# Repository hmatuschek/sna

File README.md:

# Scalar Network Analyzer

A [scalar network analyzer](https://en.wikipedia.org/wiki/Network_analyzer_%28electrical%29) (SNA) measures the amplitude of an output signal of a circuit as a function of the input frequency.

This project provides the circuit, firmware and software to implement a very simple and cheap SNA. It uses a [AD9850 DDS module](http://www.minikits.com.au/electronic-kits/dds-synthesizer/basic-dds/AD9850-DDS-01) as the programmable signal generator and a AD8307 logarithmic amplifier in conjecture with the ADC of an ATMEGA 168 (or the pin compatible ATMEGA 8/48/88/328) to record the input amplitude. The SNA hardware is interfaced via the common RS-232 using a MAX232 level converter. The firmware for the ATMEGA 168 can be found in the firmware directory.

The client software then provides a simple means of performing the measurements and displays the results. It provides two operating modes. The <emph>poll</emph> mode outputs a fixed frequency and measures the input amplitude while the <emph>scan</emph> mode records the input amplitude as a function of the output frequency. The result is then plotted (see above). 

## Hardware
As mentioned above, the [circuit](https://github.com/hmatuschek/sna/raw/master/doc/compact_scm.pdf) consists of an AD9850 DDS module (visible below) an ATMEGA 168 (partially covered in the picture) to program the DDS and to measure the output voltage of the logarithmic amplifier (AD8307, visible in the top-left corner). The logarithmic amplifier converts the input power over a 51 Ohms resistor into a voltage (0-2.5V) which is a linear function of the input power in dBm. 

The AD8307 can handle up to 17dBm (50mW). The output power of the DDS, however, is only about 0.1mW (-10dBm). To enhence the dynamic range of the SNA, a buffer amplifier (two 2N3904, circuit stolen from  [here](http://rheslip.blogspot.de/2015/08/the-simple-scalar-network-analyser.html), visible at the bottom-right corner) is used to increase the output to about 1-3mW (0-5dBm).  

The SNA is interfaced through the UART (RS-232) of the ATMEGA using a MAX232 level converter (visible in the bottom-left corner). In fact, the hardware is ARDUINO UNO compatible. By flashing the ARDUINO bootloader onto the ATMEGA, the SNA can be programmed easily via the RS-232 interface. 

The [board](https://github.com/hmatuschek/sna/raw/master/doc/compact_brd.pdf) is routed such that it is possible to assemble the circuit on a perfboard without bridges. The board dimensions are kept small. The complete circuit fits into a relatively small TEKO 2/A chassis (57 x 72 x 28 mm). For a better performance, the distance between the AD8307 logarithmic amplifier and the rest of the circuit should be increased and the AD8307 should also be shielded. Due to the lack of shielding, my prototype has a relatively large noise level of about -40dBm.

## Firmware
The firmware for the ATMEGA 168 is extremely simply. It just waits for commands received via the serial interface and either sets the frequency of the DDS module, measures the input amplitude or shuts the DDS chip down. 

### Protocol
The communication protocol is a simple binary protocol. The host (computer) sends a command to the device (SNA) and receives a response. The device never sends data without a request. 

#### Read amplitude
This command will tell the SNA to read the current amplitude.

##### Request 
```
  +------+
  | 0x01 |
  +------+
```
##### Response 
On success 
```
  +------+------+------+
  | 0x00 |  16b value  |
  +------+------+------+
```
The 16bit value (big endian) represents the 16bit fraction of the output voltage of the AD8307. This value maps linear to the dBm value where 0 represents -84dBm and 65535 17dBm.

On error  
```
  +------+
  | 0x01 |
  +------+
```

#### Set frequency
Sets the frequency of the DDS chip.

##### Request 
```
  +------+------+------+------+------+
  | 0x02 |     32b frequency word    |
  +------+------+------+------+------+
```
The 32 bit frequency word (big endian) represents the fraction of the output frequency relative to the oscillator frequency (125MHz). I.e. F_out = 125MHz * FW/2^32

##### Response 
On success 
```
  +------+
  | 0x00 |
  +------+
```
On error  
```
  +------+
  | 0x01 |
  +------+
```

#### Set frequency & read amplitude
Sets the frequency of the DDS chip and reads the current amplitude value.

##### Request 
(see set frequency command above)
```
  +------+------+------+------+------+
  | 0x03 |     32b frequency word    |
  +------+------+------+------+------+
```

##### Response 
On success 
```
  +------+------+------+
  | 0x00 |  16b value  |
  +------+------+------+
```
(see read amplitude command above)

On error  
```
  +------+
  | 0x01 |
  +------+
```

#### Shutdown DDS

This command will disable the DDS output. 

##### Request 
```
  +------+
  | 0x04 |
  +------+
```

##### Response 
On success 
```
  +------+
  | 0x00 |
  +------+
```

On error  
```
  +------+
  | 0x01 |
  +------+
```

## License
SNA - A simple scalar network analyzer. (c) 2015 Hannes Matuschek <hmatuschek at gmail dot com>

The hardware is licensed under [Createtive Commons BY-SA 4.0](https://creativecommons.org/licenses/by-sa/4.0/) and the software under [GPL 2.0+](https://www.gnu.org/licenses/old-licenses/gpl-2.0.txt) (see below).

This program is free software; you can redistribute it and/or
modify it under the terms of the GNU General Public License
as published by the Free Software Foundation; either version 2
of the License, or (at your option) any later version.</p>

This program is distributed in the hope that it will be useful,
but WITHOUT ANY WARRANTY; without even the implied warranty of
MERCHANTABILITY or FITNESS FOR A PARTICULAR PURPOSE.  See the
GNU General Public License for more details.

You should have received a copy of the GNU General Public License
along with this program; if not, write to the Free Software
Foundation, Inc., 51 Franklin Street, Fifth Floor, Boston, MA  02110-1301, USA.

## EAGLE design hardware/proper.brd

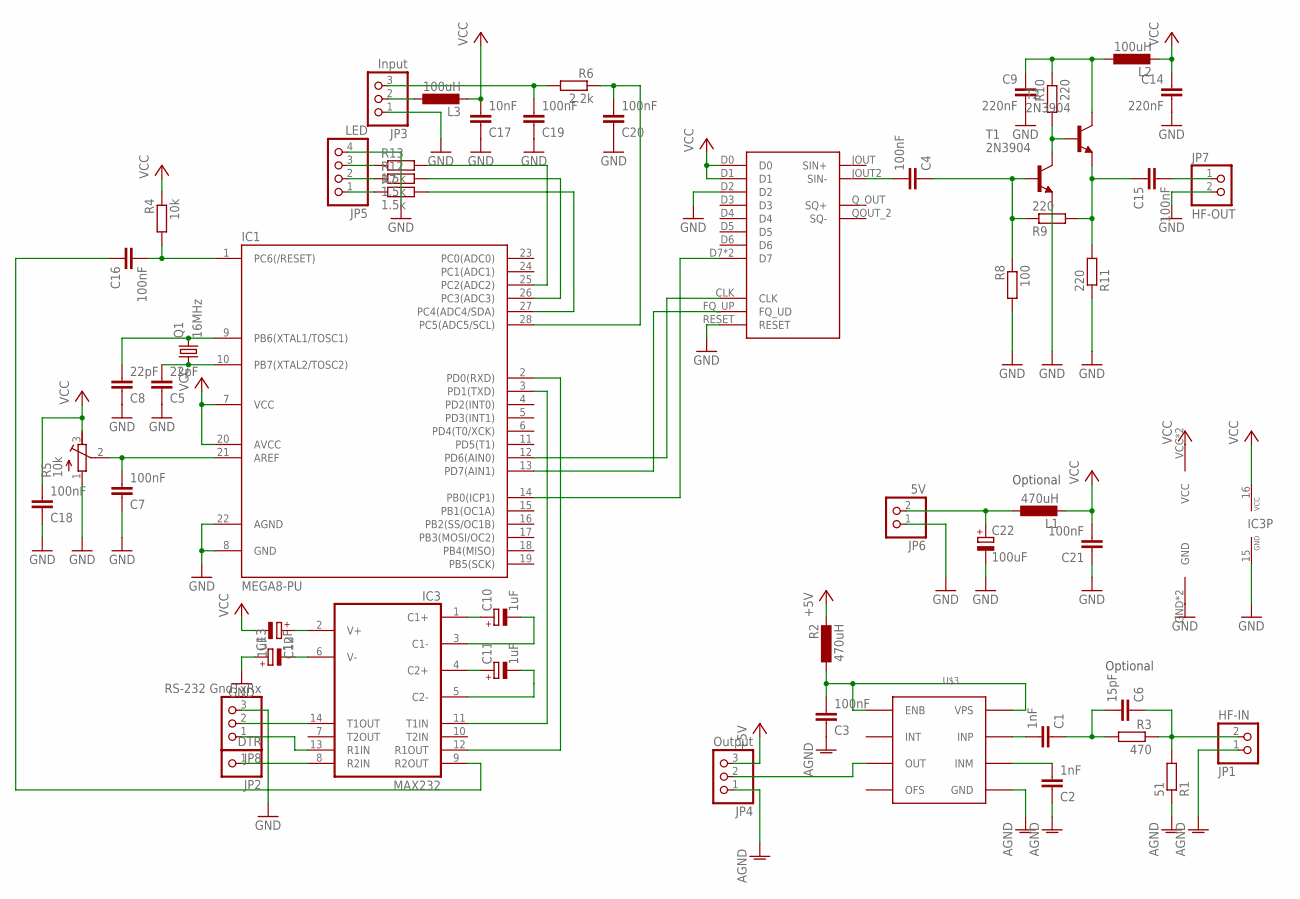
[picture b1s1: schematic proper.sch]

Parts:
C1, C2: 1nF; C025-025X050
C3, C4, C7, C19, C20, C21: 100nF; C025-025X050
C5: 22pF; C102-043X133
C6: 15pF; C050-025X075
C8: 22pF; C025-025X050
C9: 220nF; C025-025X050
C10, C11, C12, C13: 1uF; E2,5-5
C14: 220nF; C050-025X075
C15, C18: 100nF; C050-025X075
C16: 100nF; C075-032X103
C17: 10nF; C025-025X050
C22: 100uF; E2,5-6
IC1: MEGA8-PU; DIL28-3
IC3: MAX232; DIL16
JP1: HF-IN; 1X02
JP2: DTR; 1X01
JP3: Input; 1X03
JP4: Output; 1X03
JP5: LED; 1X04
JP6: 5V; 1X02
JP7: HF-OUT; 1X02
JP8: RS-232 GndTxRx; 1X03
L1: 470uH; 0207/5V
L2: 100uH; 0207/12
L3: 100uH; 0207/2V
Q1: 16MHz; HC49U-V
R1: 51; 0204V
R2: 470uH; 0204/5
R3: 470; 0204/5
R4: 10k; 0204/5
R5: 10k; RTRIM64W
R6: 2.2k; 0204V
R7, R12, R13: 1.5k; 0204/5
R8: 100; 0204V
R9, R10, R11: 220; 0204V
T1, T2: 2N3904; TO92-EBC
U$1: DDS-1
U$3: AD8307; DIL08

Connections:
+5V: JP4.3, R2.2
GND: C5.1, C7.1, C8.1, C9.2, C13.+, C14.2, C17.1, C18.1, C19.1, C20.1, C21.1, C22.-, IC1.8 (GND), IC1.22 (AGND), IC3.15 (GND), JP3.1, JP5.4, JP6.1, JP7.2, JP8.3, R5.1 (A), R8.2, R11.1, T1.E, U$1.D2, U$1.GND, U$1.GND2 (GND), U$1.RESET
unnamed: C4.2, U$1.JOUT2 (SIN-)
unnamed: C6.1, JP1.2, R1.2, R3.1
unnamed: C1.2, U$3.8 (INP)
unnamed: C2.2, U$3.1 (INM)
unnamed: C5.2, IC1.10 (PB7(XTAL2/TOSC2)), Q1.1
unnamed: C8.2, IC1.9 (PB6(XTAL1/TOSC1)), Q1.2
unnamed: C12.+, IC3.2 (V+)
unnamed: C3.2, R2.1, U$3.6 (ENB), U$3.7 (VPS)
unnamed: JP4.2, U$3.4 (OUT)
unnamed: C22.+, JP6.2, L1.1
unnamed: IC3.14 (T1OUT), JP8.2
unnamed: C1.1, C6.2, R3.2
unnamed: C4.1, R8.1, R9.1, T1.B
unnamed: C20.2, IC1.28 (PC5(ADC5/SCL)), R6.1
unnamed: IC1.13 (PD7(AIN1)), U$1.FQ_UP (FQ_UD)
unnamed: C13.-, IC3.6 (V-)
unnamed: IC1.3 (PD1(TXD)), IC3.11 (T1IN)
unnamed: IC1.12 (PD6(AIN0)), U$1.CLK
unnamed: IC1.14 (PB0(ICP1)), U$1.D7, U$1.D7_2 (D7)
unnamed: C9.1, L2.1, R10.1, T2.C
unnamed: R10.2, T1.C, T2.B
unnamed: IC1.2 (PD0(RXD)), IC3.12 (R1OUT)
unnamed: C15.2, JP7.1
unnamed: C15.1, R9.2, R11.2, T2.E
unnamed: C16.2, IC1.1 (PC6(/RESET)), R4.2
unnamed: C16.1, IC3.9 (R2OUT)
unnamed: IC3.8 (R2IN), JP2.1
unnamed: C7.2, IC1.21 (AREF), R5.2 (S)
unnamed: JP3.2, L3.1
unnamed: JP5.1, R7.1
unnamed: JP5.2, R12.1
unnamed: JP5.3, R13.1
unnamed: C2.1, C3.1, JP1.1, JP4.1, R1.1, U$3.2 (GND)
unnamed: IC3.13 (R1IN), JP8.1
unnamed: IC1.27 (PC4(ADC4/SDA)), R7.2
unnamed: IC1.26 (PC3(ADC3)), R12.2
unnamed: IC1.25 (PC2(ADC2)), R13.2
unnamed: C10.+, IC3.1 (C1+)
unnamed: C10.-, IC3.3 (C1-)
unnamed: C11.+, IC3.4 (C2+)
unnamed: C11.-, IC3.5 (C2-)
unnamed: C19.2, JP3.3, R6.2
VCC: C12.-, C14.1, C17.2, C18.2, C21.2, IC1.7 (VCC), IC1.20 (AVCC), IC3.16 (VCC), L1.2, L2.2, L3.2, R4.1, R5.3 (E), U$1.D0, U$1.D1, U$1.VCC, U$1.VCC2 (VCC)

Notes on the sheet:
Optional

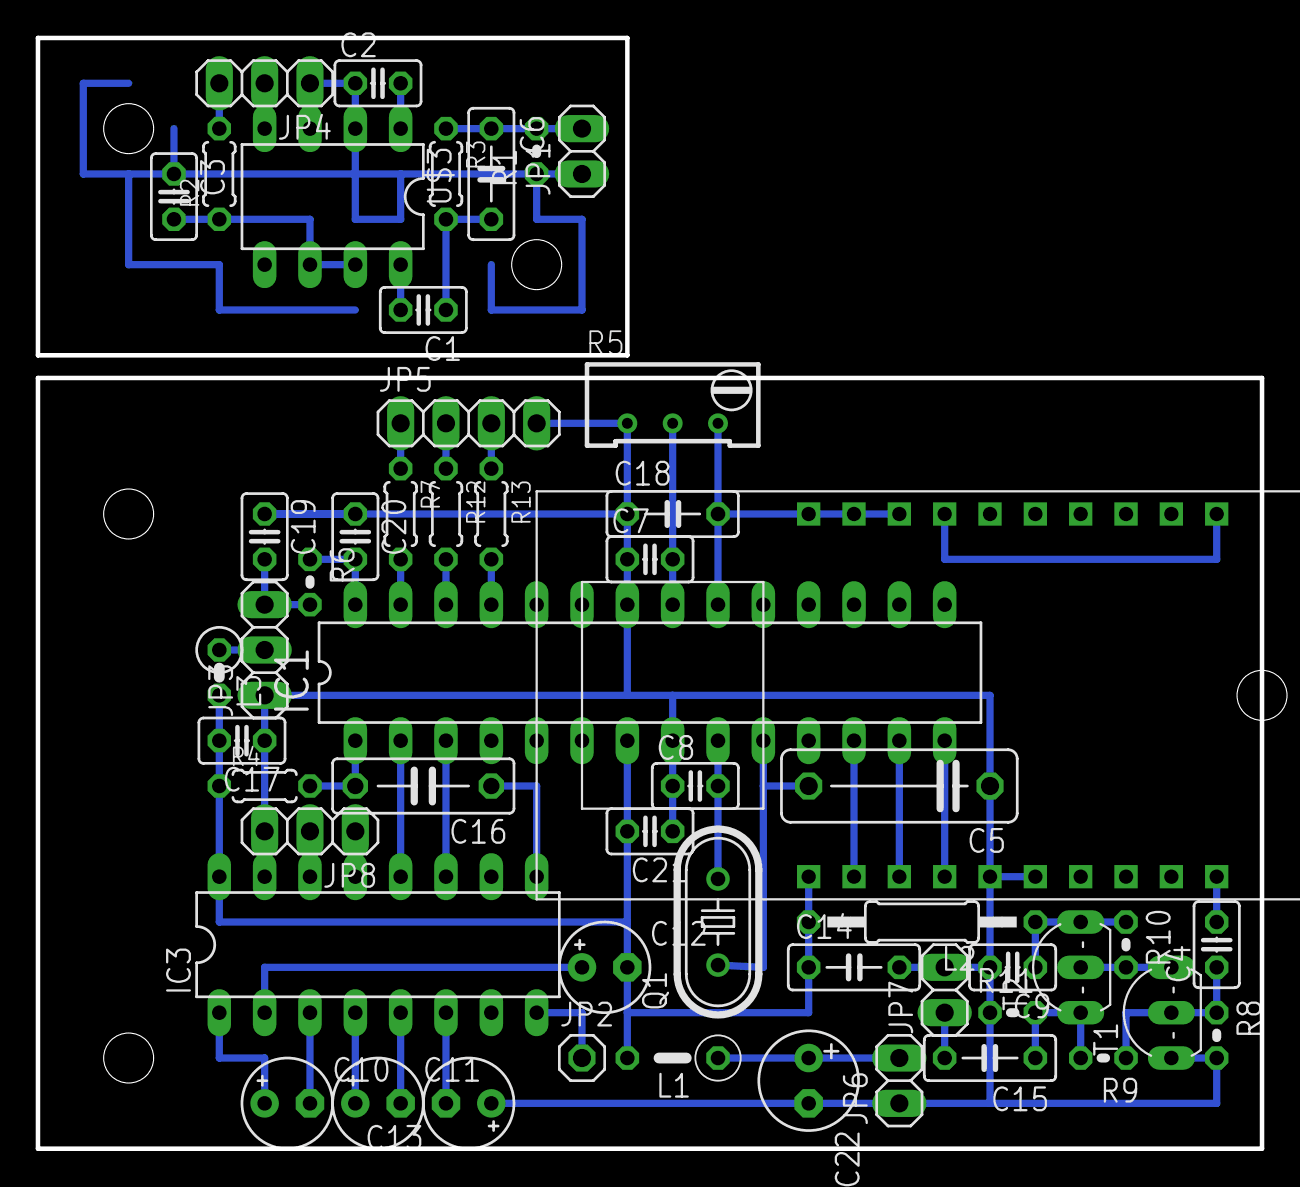
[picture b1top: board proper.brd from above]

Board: 2 copper layers, 68.6 x 62.2 mm, 53 parts (0 on the bottom side), 45 nets.

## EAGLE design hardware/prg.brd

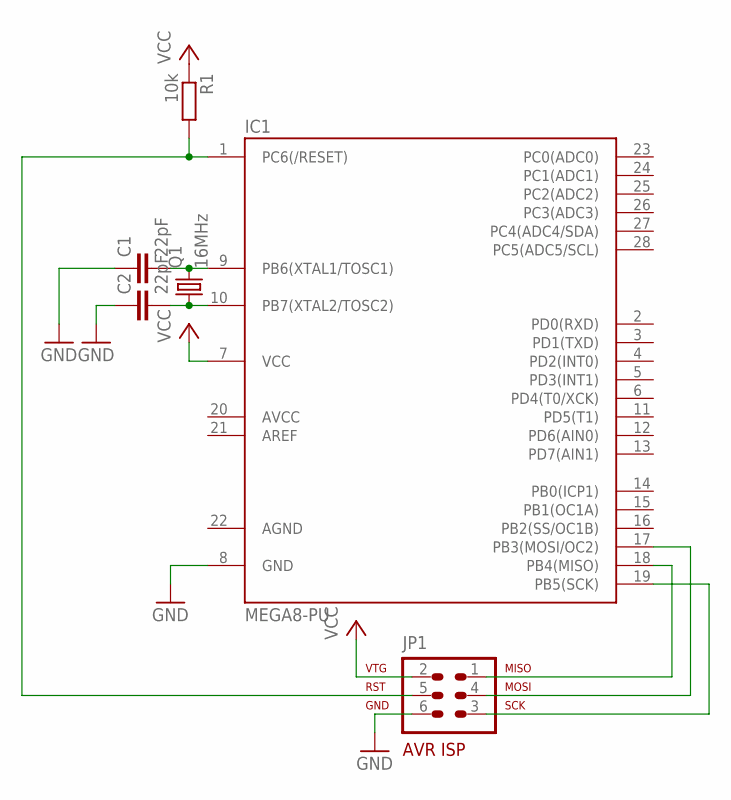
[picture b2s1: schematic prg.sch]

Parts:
C1: 22pF; C025-025X050
C2: 22pF; C050-025X075
IC1: MEGA8-PU; DIL28-3
JP1: AVR-ISP-6
Q1: 16MHz; HC49/S
R1: 10k; 0204/7

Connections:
AGND: IC1.22 (AGND)
GND: C1.1, C2.1, IC1.8 (GND), JP1.6
unnamed: IC1.19 (PB5(SCK)), JP1.3
unnamed: IC1.17 (PB3(MOSI/OC2)), JP1.4
unnamed: IC1.18 (PB4(MISO)), JP1.1
unnamed: C2.2, IC1.10 (PB7(XTAL2/TOSC2)), Q1.1
unnamed: C1.2, IC1.9 (PB6(XTAL1/TOSC1)), Q1.2
unnamed: IC1.1 (PC6(/RESET)), JP1.5, R1.2
VCC: IC1.7 (VCC), JP1.2, R1.1

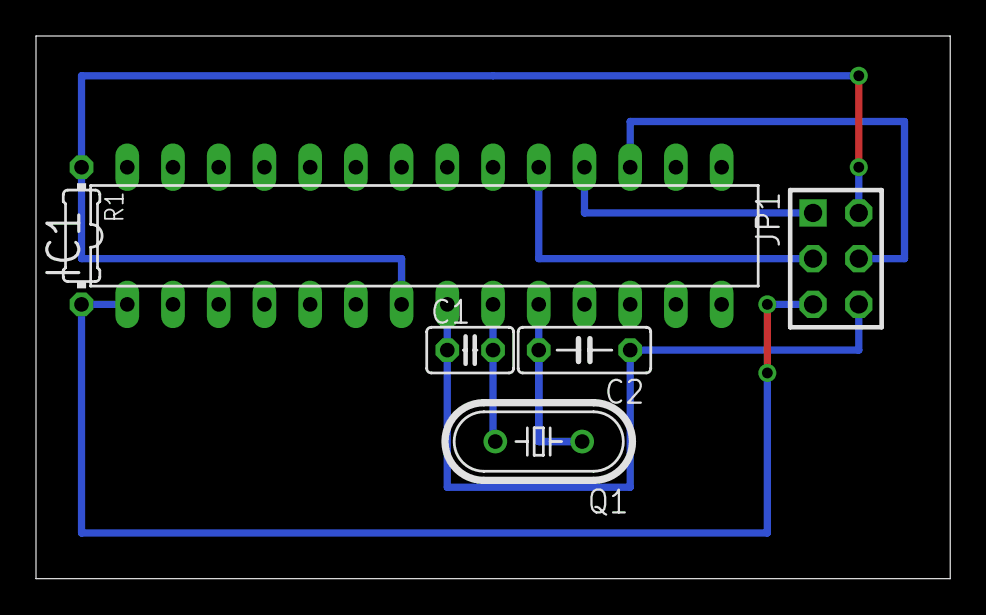
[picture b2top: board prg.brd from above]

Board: 2 copper layers, 50.8 x 30.1 mm, 6 parts (0 on the bottom side), 8 nets.

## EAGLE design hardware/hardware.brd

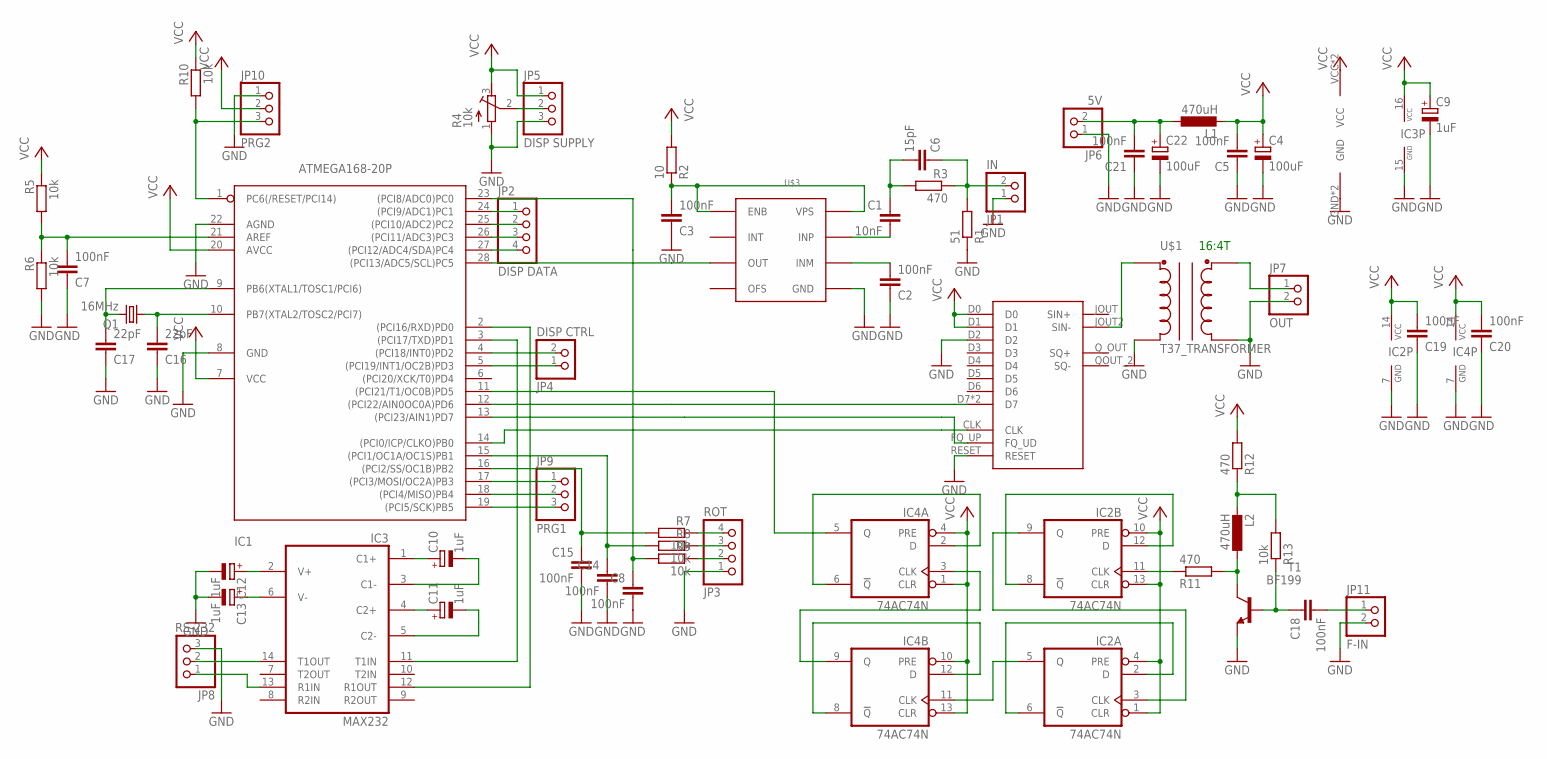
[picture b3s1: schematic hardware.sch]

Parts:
C1: 10nF; C025-025X050
C2, C3, C5, C7, C8, C19, C20, C21: 100nF; C025-025X050
C4, C22: 100uF; E2,5-6
C6: 15pF; C025-025X050
C9, C12, C13: 1uF; E2,5-6
C10: 1uF; E5-5
C11: 1uF; E2,5-5
C14, C15: 100nF; C050-025X075
C16, C17: 22pF; C050-025X075
C18: 100nF; C075-032X103
IC1: ATMEGA168-20P; DIL28-3
IC2, IC4: 74AC74N; DIL14
IC3: MAX232; DIL16
JP1: IN; 1X02
JP2: DISP DATA; 1X04
JP3: ROT; 1X04
JP4: DISP CTRL; 1X02
JP5: DISP SUPPLY; 1X03
JP6: 5V; 1X02
JP7: OUT; 1X02
JP8: RS-232; 1X03
JP9: PRG1; 1X03
JP10: PRG2; 1X03
JP11: F-IN; 1X02
L1, L2: 470uH; 0204/7
Q1: 16MHz; HC49/S
R1: 51; 0204V
R2: 10; 0207/10
R3: 470; 0204V
R4: 10k; RTRIM3339P
R5, R6, R8, R13: 10k; 0204V
R7: 10k; 0204/5
R9: 10k; 0207/10
R10: 10k; 0207/15
R11: 470; 0207/10
R12: 470; 0204/7
T1: BF199; TO92-CEB
U$1: T37_TRANSFORMER
U$2: DDS-1
U$3: AD8307; DIL08

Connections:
GND: C2.1, C3.1, C4.-, C5.1, C7.1, C8.2, C9.-, C12.-, C13.-, C14.2, C15.2, C16.1, C17.1, C19.1, C20.1, C21.1, C22.-, IC1.8 (GND), IC1.22 (AGND), IC2.7 (GND), IC3.15 (GND), IC4.7 (GND), JP1.1, JP3.1, JP5.3, JP6.1, JP7.2, JP8.3, JP10.1, JP11.2, R1.1, R4.1 (A), R6.2, T1.E, U$1.C1A, U$1.C2A, U$2.D2, U$2.GND, U$2.GND2 (GND), U$2.RESET, U$3.2 (GND)
unnamed: IC1.17 ((PCI3/MOSI/OC2A)PB3), JP9.1
unnamed: C6.1, JP1.2, R1.2, R3.1
unnamed: C1.2, U$3.8 (INP)
unnamed: C2.2, U$3.1 (INM)
unnamed: IC1.18 ((PCI4/MISO)PB4), JP9.2
unnamed: IC1.19 ((PCI5/SCK)PB5), JP9.3
unnamed: IC1.1 (PC6(/RESET/PCI14)), JP10.3, R10.2
unnamed: C3.2, R2.1, U$3.6 (ENB), U$3.7 (VPS)
unnamed: IC1.28 ((PCI13/ADC5/SCL)PC5), U$3.4 (OUT)
unnamed: C21.2, C22.+, JP6.2, L1.1
unnamed: IC3.14 (T1OUT), JP8.2
unnamed: C1.1, C6.2, R3.2
unnamed: U$1.C1B, U$2.JOUT2 (SIN-)
unnamed: JP7.1, U$1.C2B
unnamed: IC1.13 ((PCI23/AIN1)PD7), U$2.FQ_UP (FQ_UD)
unnamed: IC1.27 ((PCI12/ADC4/SDA)PC4), JP2.4
unnamed: IC1.3 ((PCI17/TXD)PD1), IC3.11 (T1IN)
unnamed: IC1.26 ((PCI11/ADC3)PC3), JP2.3
unnamed: IC1.25 ((PCI10/ADC2)PC2), JP2.2
unnamed: IC1.24 ((PCI9/ADC1)PC1), JP2.1
unnamed: C15.1, IC1.16 ((PCI2/SS/OC1B)PB2), R7.2
unnamed: IC1.2 ((PCI16/RXD)PD0), IC3.12 (R1OUT)
unnamed: C14.1, IC1.15 ((PCI1/OC1A/OC1S)PB1), R8.2
unnamed: JP3.4, R7.1
unnamed: IC1.4 ((PCI18/INT0)PD2), JP4.2
unnamed: IC1.14 ((PCI0/ICP/CLKO)PB0), U$2.CLK
unnamed: IC1.5 ((PCI19/INT1/OC2B)PD3), JP4.1
unnamed: JP5.2, R4.2 (S)
unnamed: C7.2, IC1.21 (AREF), R5.2, R6.1
unnamed: IC1.12 ((PCI22/AIN0OC0A)PD6), U$2.D7, U$2.D7_2 (D7)
unnamed: JP3.3, R8.1
unnamed: JP3.2, R9.1
unnamed: C8.1, IC1.23 ((PCI8/ADC0)PC0), R9.2
unnamed: IC3.13 (R1IN), JP8.1
unnamed: C12.+, IC3.2 (V+)
unnamed: C13.+, IC3.6 (V-)
unnamed: C16.2, IC1.10 (PB7(XTAL2/TOSC2/PCI7)), Q1.1
unnamed: C10.+, IC3.1 (C1+)
unnamed: C10.-, IC3.3 (C1-)
unnamed: C11.+, IC3.4 (C2+)
unnamed: C11.-, IC3.5 (C2-)
unnamed: C17.2, IC1.9 (PB6(XTAL1/TOSC1/PCI6)), Q1.2
unnamed: IC4.2 (D), IC4.6 (!Q)
unnamed: IC1.11 ((PCI21/T1/OC0B)PD5), IC4.5 (Q)
unnamed: IC2.8 (!Q), IC2.12 (D)
unnamed: IC2.2 (D), IC2.6 (!Q)
unnamed: IC4.8 (!Q), IC4.12 (D)
unnamed: IC2.3 (CLK), IC2.9 (Q)
unnamed: IC2.5 (Q), IC4.11 (CLK)
unnamed: IC4.3 (CLK), IC4.9 (Q)
unnamed: IC2.11 (CLK), R11.1
unnamed: L2.1, R11.2, T1.C
unnamed: L2.2, R12.1, R13.2
unnamed: C18.1, R13.1, T1.B
unnamed: C18.2, JP11.1
VCC: C4.+, C5.2, C9.+, C19.2, C20.2, IC1.7 (VCC), IC1.20 (AVCC), IC2.1 (CLR), IC2.4 (PRE), IC2.10 (PRE), IC2.13 (CLR), IC2.14 (VCC), IC3.16 (VCC), IC4.1 (CLR), IC4.4 (PRE), IC4.10 (PRE), IC4.13 (CLR), IC4.14 (VCC), JP5.1, JP10.2, L1.2, R2.2, R4.3 (E), R5.1, R10.1, R12.2, U$2.D0, U$2.D1, U$2.VCC, U$2.VCC2 (VCC)

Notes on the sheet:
16:4T

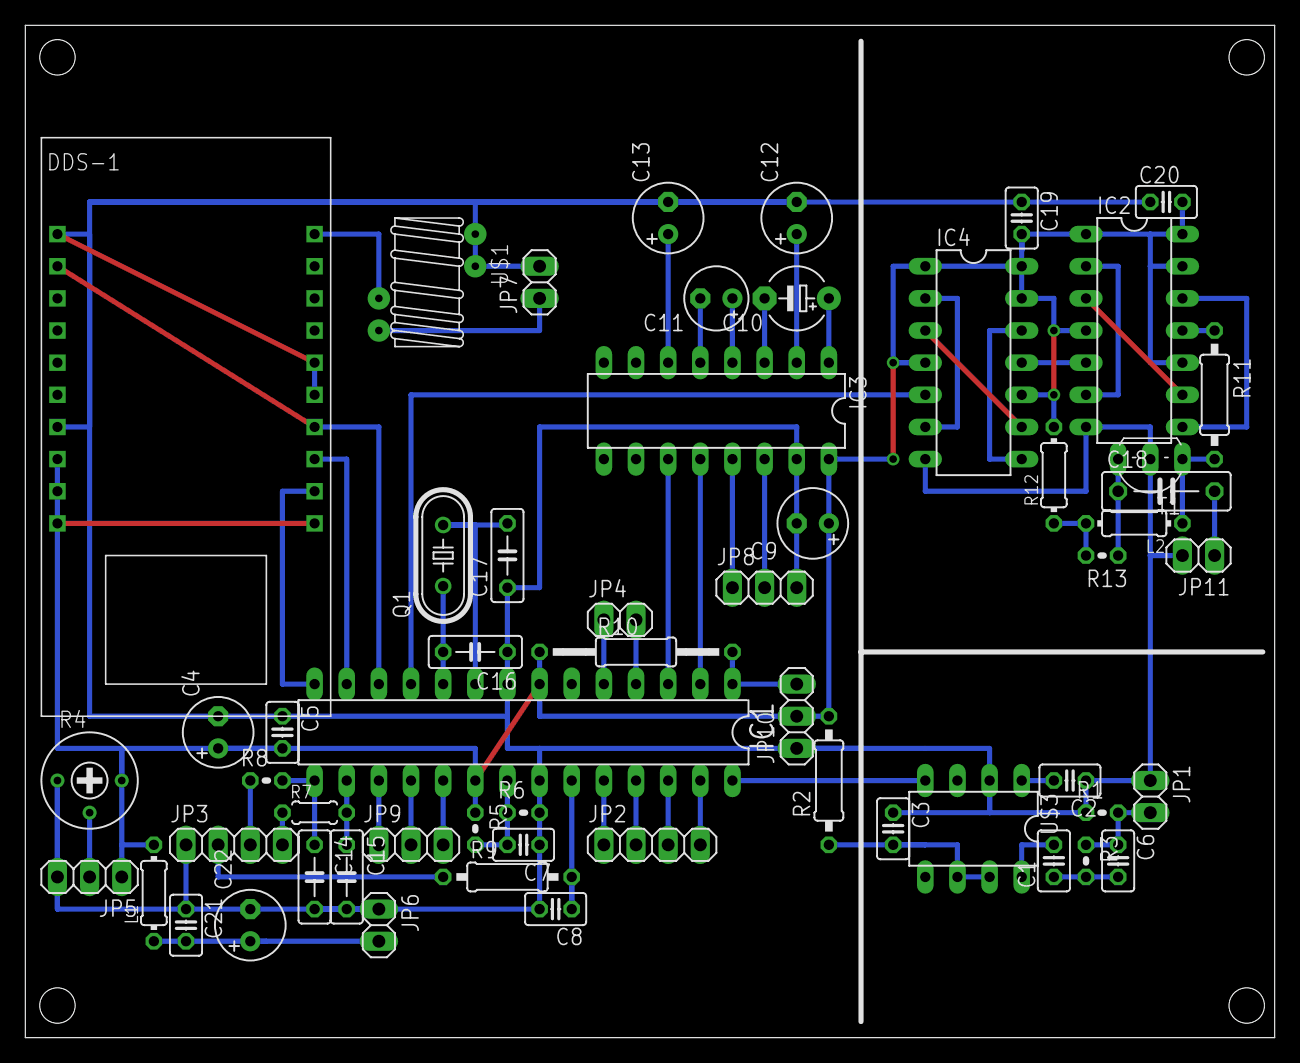
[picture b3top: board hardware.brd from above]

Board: 2 copper layers, 98.7 x 80.0 mm, 57 parts (0 on the bottom side), 57 nets.

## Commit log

2015-07-29 Initial.
2015-07-29 Added port config.
2015-07-31 Updated hardware.
2015-08-05 Fixed circuit and board.
2015-08-22 Fixes.
2015-08-23 Fixed readme.
2015-08-23 Fixed board and schematic PDFs.
2015-08-23 Client now handles timeouts.
2015-08-23 Fixed firmware to use ADC noise reduction mode.
2017-03-06 Fixed minors, added win build.
2017-03-12 Fixed minor.
2017-03-12 Added debug message.
2017-03-12 Fixed debug message.
2017-03-15 Fixed inttypes.
2017-03-15 Updated plot library to QCustomPlot.
